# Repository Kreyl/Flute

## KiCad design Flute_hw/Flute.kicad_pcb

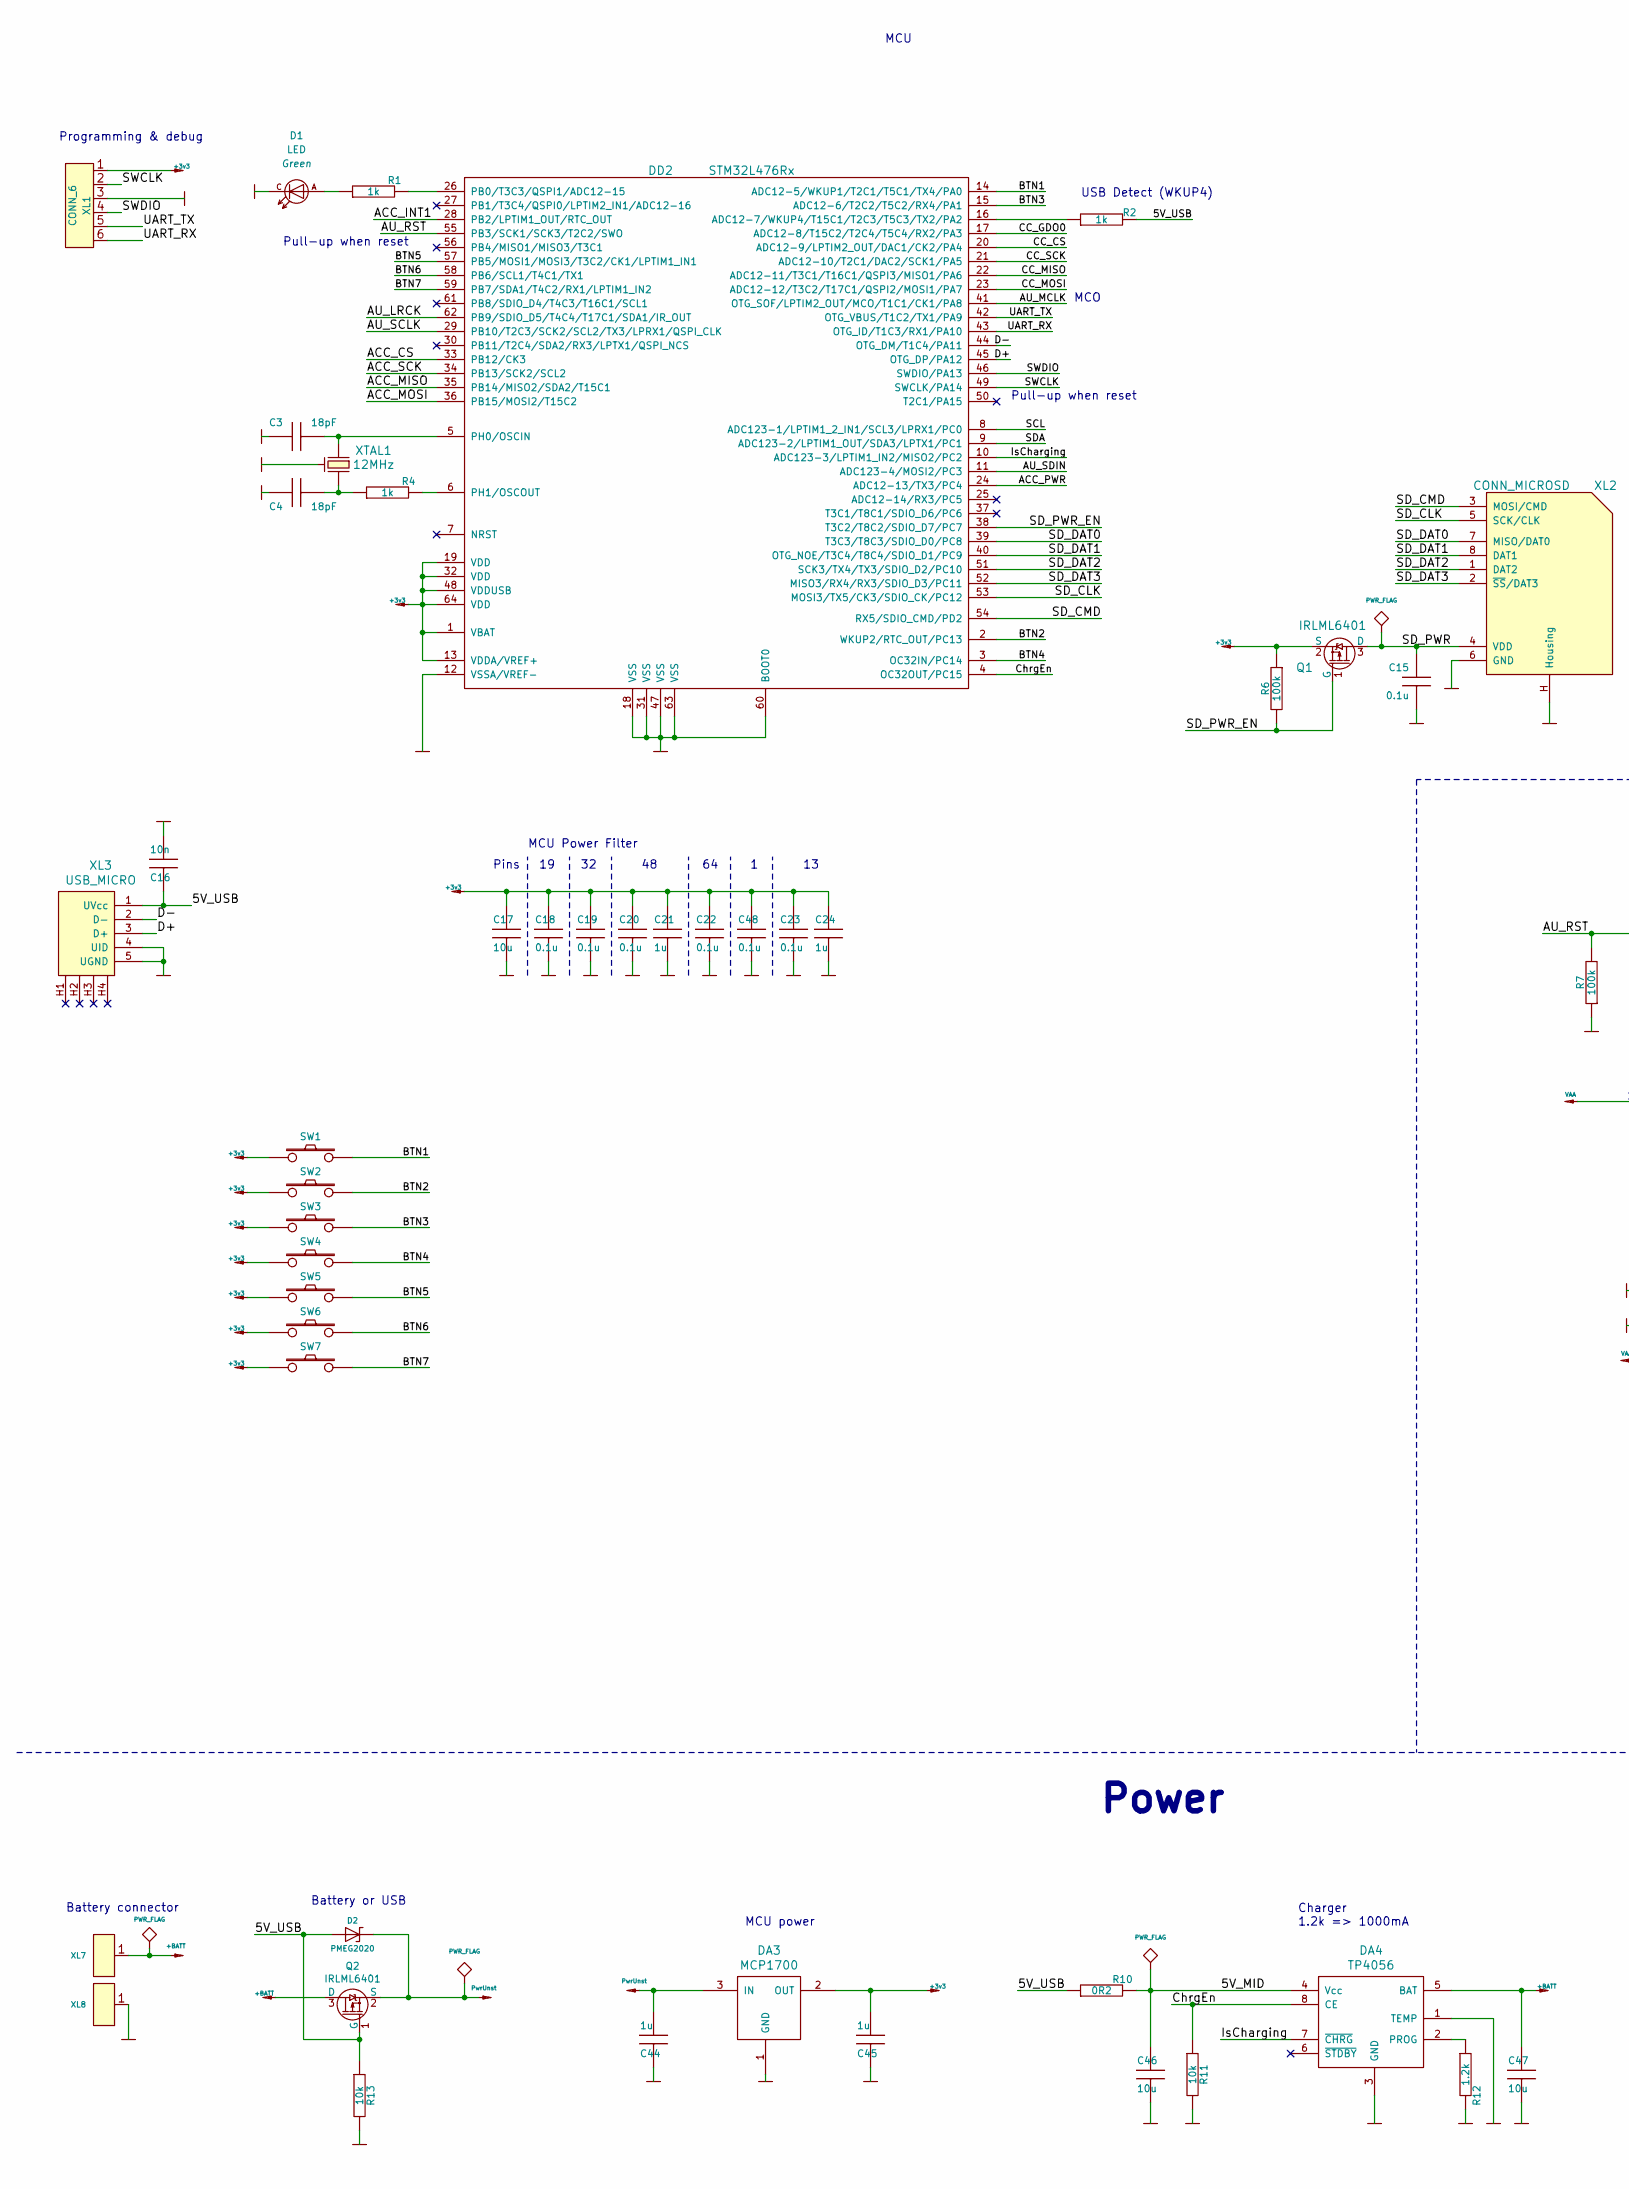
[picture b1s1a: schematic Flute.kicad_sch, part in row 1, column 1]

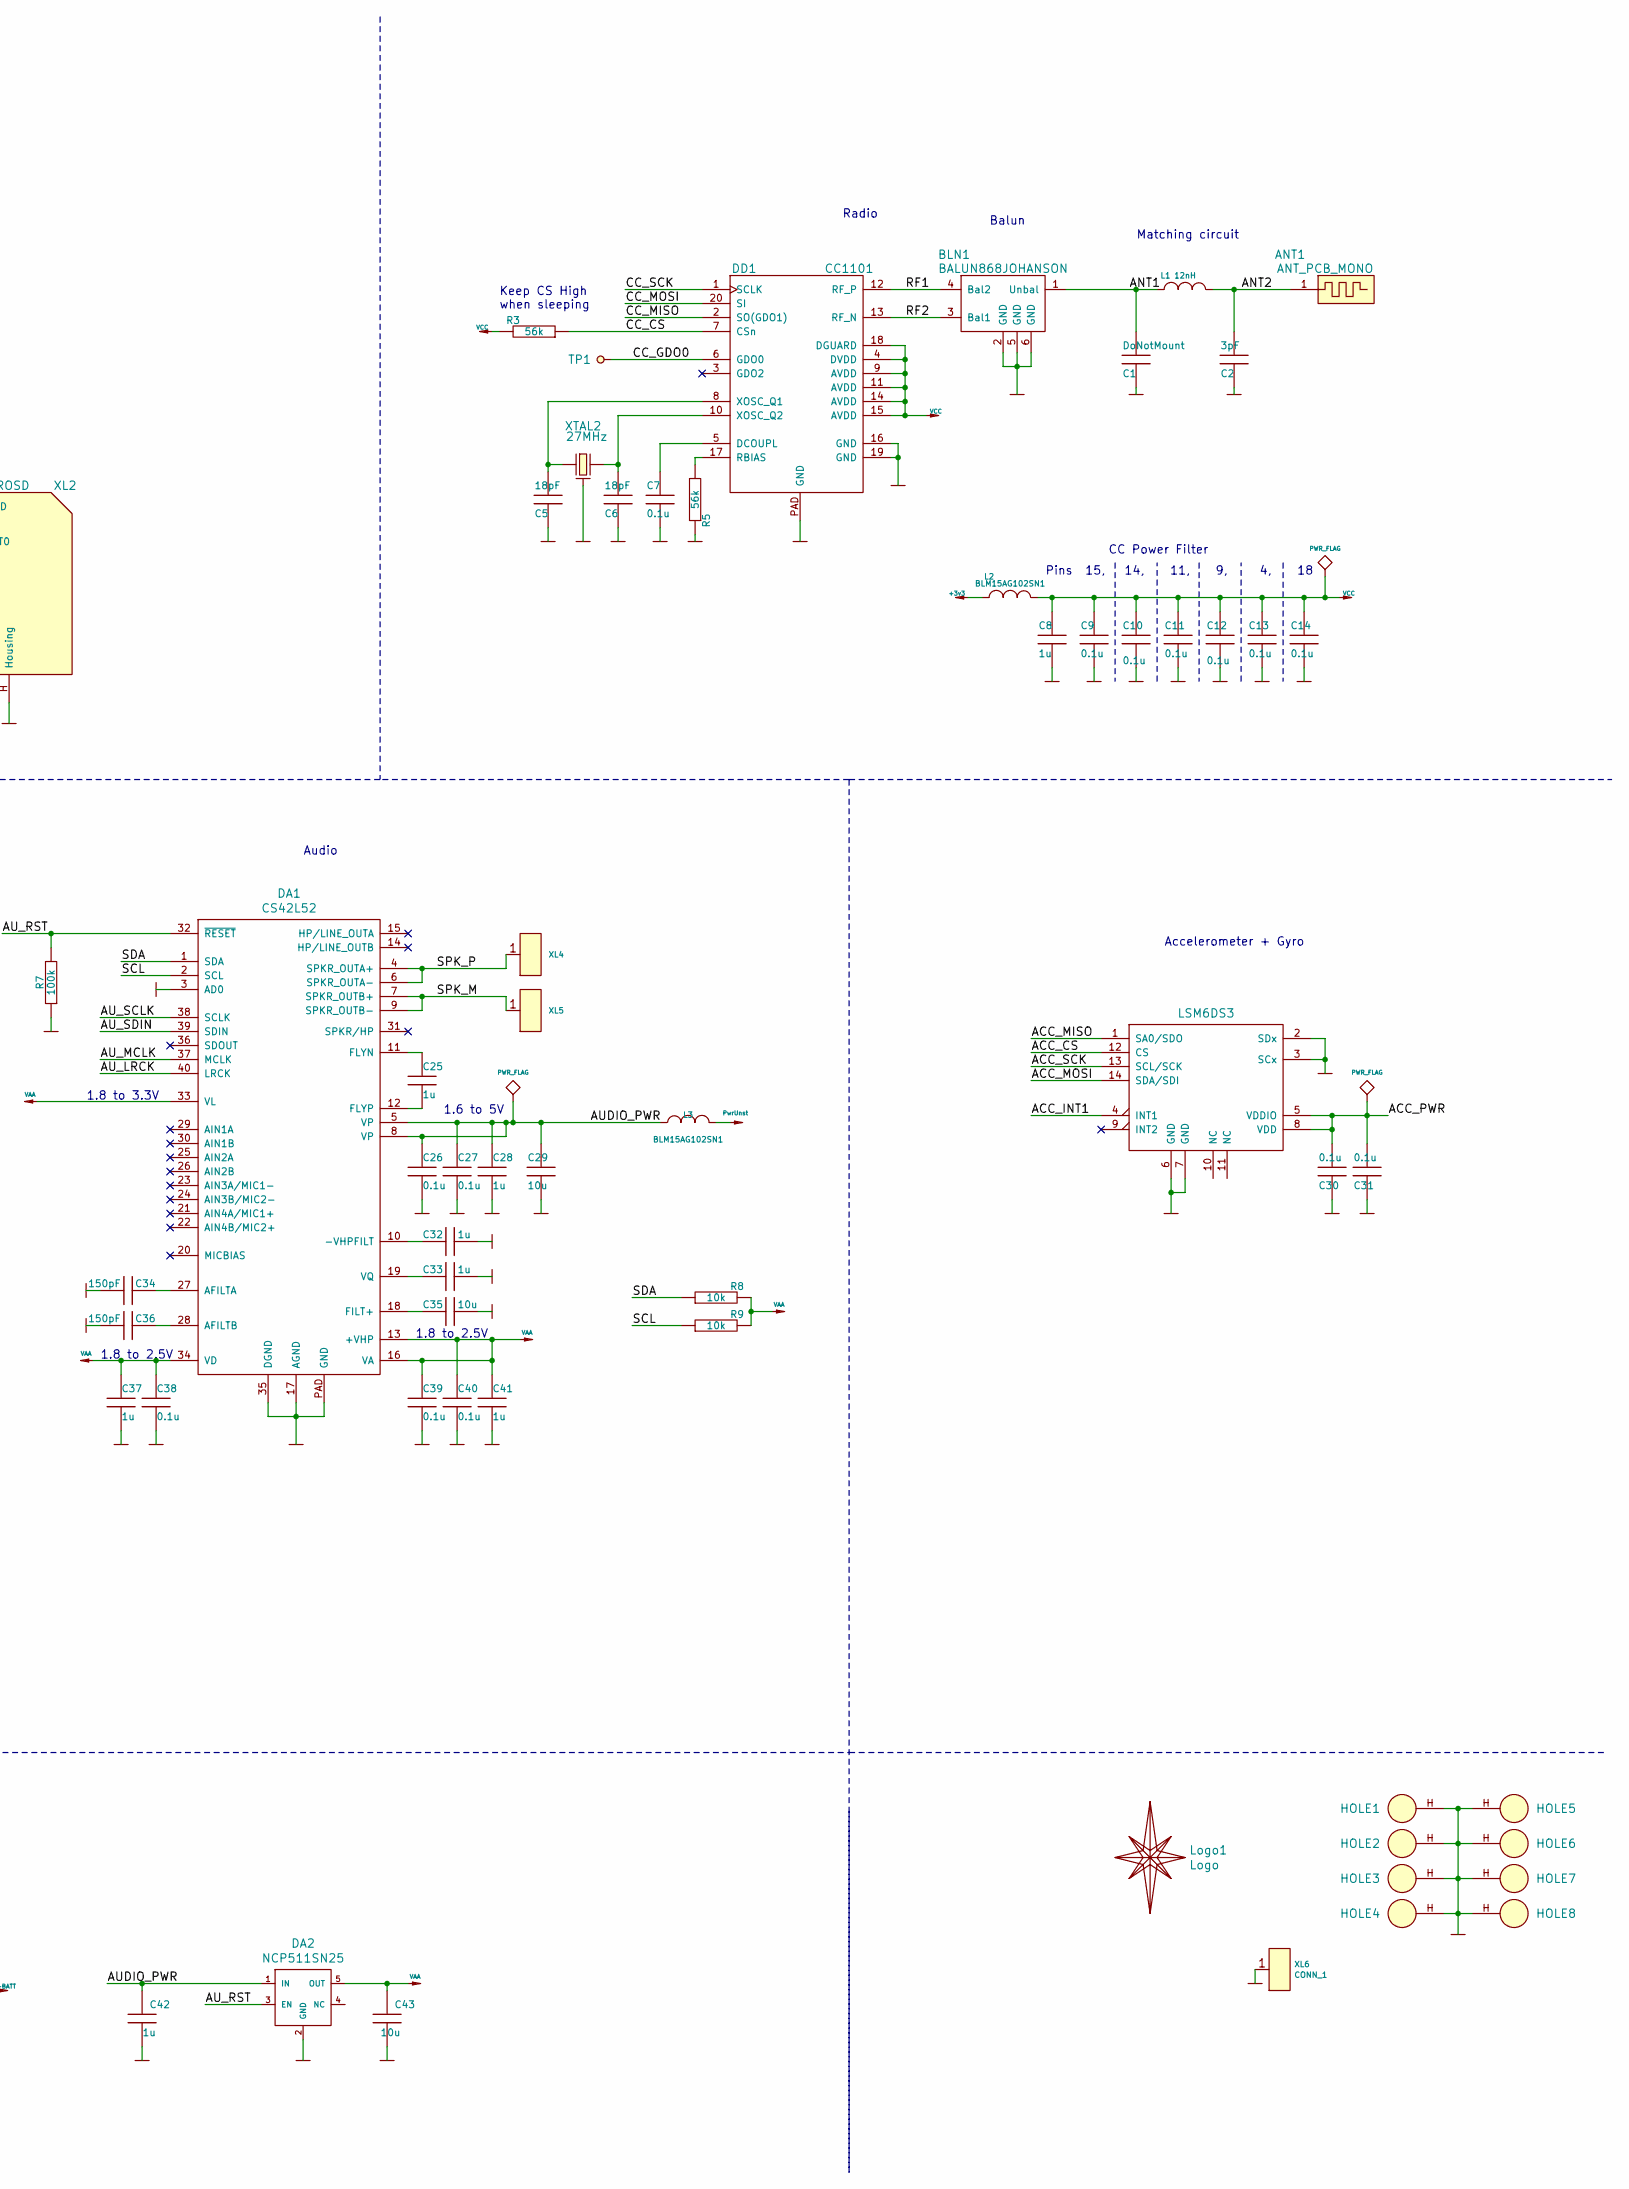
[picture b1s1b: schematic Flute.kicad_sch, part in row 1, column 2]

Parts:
ANT1: ANT_PCB_MONO; Flute_868_inverted
BLN1: BALUN868JOHANSON; BALUN_JOHANSON868
C1: DoNotMount; CAP_0402
C2: 3pF; CAP_0402
C3, C4, C5, C6: 18pF; CAP_0603_Silks
C7, C9, C10, C11, C12, C13, C14, C15, C18, C19, C20, C22, C23, C26, C27, C30, C31, C38, C39, C40, C48: 0.1u; CAP_0603_Silks
C8, C21, C24, C25, C28, C32, C33, C37, C41, C42, C44, C45: 1u; CAP_0603_Silks
C16: 10n; CAP_0603_Silks
C17, C29, C35, C43, C46, C47: 10u; CAP_0603_Silks
C34, C36: 150pF; CAP_0603_Silks
D1: LED; LED_0603
D2: PMEG2020; SOD323
DA1: CS42L52; QFN40
DA2: NCP511SN25; SOT23-5
DA3: MCP1700; SOT23-3A
DA4: TP4056; SO8_150MIL
DD1: CC1101; QFN20
DD2: STM32L476Rx; LQFP64
DD3: LSM6DS3; 14_3x2d5_p0d5
HOLE1, HOLE2, HOLE3, HOLE4, HOLE5, HOLE6, HOLE7, HOLE8: HOLE_METALLED; Hole2d2_out3d5mm
L1: 12nH; IND_0402
L2, L3: BLM15AG102SN1; IND_0402
Logo1: Logo; Ostranna_12d7_10d1
Q1, Q2: IRLML6401; SOT23-3
R1, R2, R4: 1k; RES_0603
R3, R5: 56k; RES_0603
R6, R7: 100k; RES_0603
R8, R9, R11, R13: 10k; RES_0603
R10: 0R2; RES_1206
R12: 1.2k; RES_0603
SW1, SW2, SW3, SW4, SW5, SW6, SW7: BUTTON; BTN_4x4_SMD
TP1: TESTPOINT; TESTPOINT_1MM
XL1: CONN_6; PLS-6_LOCK
XL2: CONN_MICROSD; MICROSD_CAP_FIX05A
XL3: USB_MICRO; USBmicro_MOLEX_1050170001
XL4, XL5: CONN_1; Oval3x1.5
XL6: CONN_1; PLS-1Rnd
XL7, XL8: CONN_1; Square_1MM5
XTAL1: 12MHz; 03225C4
XTAL2: 27MHz; 03225C4

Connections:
+3v3: C17.2, C18.2, C19.2, C20.2, C21.2, C22.2, C23.2, C24.2, C45.1, C48.2, DA3.2 (OUT), DD2.1 (VBAT), DD2.13 (VDDA/VREF+), DD2.19 (VDD), DD2.32 (VDD), DD2.48 (VDDUSB), DD2.64 (VDD), L2.2, Q1.2 (S), R6.1, SW1.1, SW2.1, SW3.1, SW4.1, SW5.1, SW6.1, SW7.1, XL1.1
+BATT: C47.2, DA4.5 (BAT), Q2.3 (D), XL7.1
/5V_MID: C46.2, DA4.4 (Vcc), R10.2
/5V_USB: C16.2, D2.A, Q2.1 (G), R2.2, R10.1, R13.1, XL3.1 (UVcc)
/ACC_CS: DD2.33 (PB12/CK3), DD3.12 (CS)
/ACC_INT1: DD2.28 (PB2/LPTIM1_OUT/RTC_OUT), DD3.4 (INT1)
/ACC_MISO: DD2.35 (PB14/MISO2/SDA2/T15C1), DD3.1 (SA0/SDO)
/ACC_MOSI: DD2.36 (PB15/MOSI2/T15C2), DD3.14 (SDA/SDI)
/ACC_PWR: C30.1, C31.1, DD2.24 (ADC12-13/TX3/PC4), DD3.5 (VDDIO), DD3.8 (VDD)
/ACC_SCK: DD2.34 (PB13/SCK2/SCL2), DD3.13 (SCL/SCK)
/ANT1: BLN1.1 (Unbal), C1.1, L1.2
/ANT2: ANT1.1, C2.1, L1.1
/AUDIO_PWR: C26.1, C27.1, C28.1, C29.2, C42.1, DA1.5 (VP), DA1.8 (VP), DA2.1 (IN), L3.1
/AU_LRCK: DA1.40 (LRCK), DD2.62 (PB9/SDIO_D5/T4C4/T17C1/SDA1/IR_OUT)
/AU_MCLK: DA1.37 (MCLK), DD2.41 (OTG_SOF/LPTIM2_OUT/MCO/T1C1/CK1/PA8)
/AU_RST: DA1.32 (~RESET), DA2.3 (EN), DD2.55 (PB3/SCK1/SCK3/T2C2/SWO), R7.2
/AU_SCLK: DA1.38 (SCLK), DD2.29 (PB10/T2C3/SCK2/SCL2/TX3/LPRX1/QSPI_CLK)
/AU_SDIN: DA1.39 (SDIN), DD2.11 (ADC123-4/MOSI2/PC3)
/BTN1: DD2.14 (ADC12-5/WKUP1/T2C1/T5C1/TX4/PA0), SW1.2
/BTN2: DD2.2 (WKUP2/RTC_OUT/PC13), SW2.2
/BTN3: DD2.15 (ADC12-6/T2C2/T5C2/RX4/PA1), SW3.2
/BTN4: DD2.3 (OC32IN/PC14), SW4.2
/BTN5: DD2.57 (PB5/MOSI1/MOSI3/T3C2/CK1/LPTIM1_IN1), SW5.2
/BTN6: DD2.58 (PB6/SCL1/T4C1/TX1), SW6.2
/BTN7: DD2.59 (PB7/SDA1/T4C2/RX1/LPTIM1_IN2), SW7.2
/CC_CS: DD1.7 (CSn), DD2.20 (ADC12-9/LPTIM2_OUT/DAC1/CK2/PA4), R3.1
/CC_GDO0: DD1.6 (GDO0), DD2.17 (ADC12-8/T15C2/T2C4/T5C4/RX2/PA3), TP1.1
/CC_MISO: DD1.2 (SO(GDO1)), DD2.22 (ADC12-11/T3C1/T16C1/QSPI3/MISO1/PA6)
/CC_MOSI: DD1.20 (SI), DD2.23 (ADC12-12/T3C2/T17C1/QSPI2/MOSI1/PA7)
/CC_SCK: DD1.1 (SCLK), DD2.21 (ADC12-10/T2C1/DAC2/SCK1/PA5)
/ChrgEn: DA4.8 (CE), DD2.4 (OC32OUT/PC15), R11.1
/D+: DD2.45 (OTG_DP/PA12), XL3.3 (D+)
/D-: DD2.44 (OTG_DM/T1C4/PA11), XL3.2 (D-)
/IsCharging: DA4.7 (~CHRG), DD2.10 (ADC123-3/LPTIM1_IN2/MISO2/PC2)
/RF1: BLN1.4 (Bal2), DD1.12 (RF_P)
/RF2: BLN1.3 (Bal1), DD1.13 (RF_N)
/SCL: DA1.2 (SCL), DD2.8 (ADC123-1/LPTIM1_2_IN1/SCL3/LPRX1/PC0), R9.1
/SDA: DA1.1 (SDA), DD2.9 (ADC123-2/LPTIM1_OUT/SDA3/LPTX1/PC1), R8.1
/SD_CLK: DD2.53 (MOSI3/TX5/CK3/SDIO_CK/PC12), XL2.5 (SCK/CLK)
/SD_CMD: DD2.54 (RX5/SDIO_CMD/PD2), XL2.3 (MOSI/CMD)
/SD_DAT0: DD2.39 (T3C3/T8C3/SDIO_D0/PC8), XL2.7 (MISO/DAT0)
/SD_DAT1: DD2.40 (OTG_NOE/T3C4/T8C4/SDIO_D1/PC9), XL2.8 (DAT1)
/SD_DAT2: DD2.51 (SCK3/TX4/TX3/SDIO_D2/PC10), XL2.1 (DAT2)
/SD_DAT3: DD2.52 (MISO3/RX4/RX3/SDIO_D3/PC11), XL2.2 (~SS~/DAT3)
/SD_PWR: C15.1, Q1.3 (D), XL2.4 (VDD)
/SD_PWR_EN: DD2.38 (T3C2/T8C2/SDIO_D7/PC7), Q1.1 (G), R6.2
/SPK_M: DA1.7 (SPKR_OUTB+), DA1.9 (SPKR_OUTB-), XL5.1
/SPK_P: DA1.4 (SPKR_OUTA+), DA1.6 (SPKR_OUTA-), XL4.1
/SWCLK: DD2.49 (SWCLK/PA14), XL1.2
/SWDIO: DD2.46 (SWDIO/PA13), XL1.4
/UART_RX: DD2.43 (OTG_ID/T1C3/RX1/PA10), XL1.6
/UART_TX: DD2.42 (OTG_VBUS/T1C2/TX1/PA9), XL1.5
GND: BLN1.2 (GND), BLN1.5 (GND), BLN1.6 (GND), C1.2, C2.2, C3.2, C4.2, C5.2, C6.2, C7.1, C8.2, C9.2, C10.2, C11.2, C12.2, C13.2, C14.2, C15.2, C16.1, C17.1, C18.1, C19.1, C20.1, C21.1, C22.1, C23.1, C24.1, C26.2, C27.2, C28.2, C29.1, C30.2, C31.2, C32.1, C33.1, C34.1, C35.1, C36.1, C37.2, C38.2, C39.2, C40.2, C41.2, C42.2, C43.2, C44.2, C45.2, C46.1, C47.1, C48.1, D1.C, DA1.3 (AD0), DA1.17 (AGND), DA1.35 (DGND), DA1.PAD (GND), DA2.2 (GND), DA3.1 (GND), DA4.1 (TEMP), DA4.3 (GND), DD1.16 (GND), DD1.19 (GND), DD1.PAD (GND), DD2.12 (VSSA/VREF-), DD2.18 (VSS), DD2.31 (VSS), DD2.47 (VSS), DD2.60 (BOOT0), DD2.63 (VSS), DD3.2 (SDx), DD3.3 (SCx), DD3.6 (GND), DD3.7 (GND), HOLE1.H, HOLE2.H, HOLE3.H, HOLE4.H, HOLE5.H, HOLE6.H, HOLE7.H, HOLE8.H, R5.2, R7.1, R11.2, R12.2, R13.2, XL1.3, XL2.6 (GND), XL2.H (Housing), XL3.4 (UID), XL3.5 (UGND), XL6.1, XL8.1, XTAL1.H, XTAL2.H
unnamed: C3.1, DD2.5 (PH0/OSCIN), XTAL1.1
unnamed: C4.1, R4.1, XTAL1.2
unnamed: C5.1, DD1.8 (XOSC_Q1), XTAL2.1
unnamed: C6.1, DD1.10 (XOSC_Q2), XTAL2.2
unnamed: C7.2, DD1.5 (DCOUPL)
unnamed: C25.1, DA1.11 (FLYN)
unnamed: C25.2, DA1.12 (FLYP)
unnamed: C32.2, DA1.10 (-VHPFILT)
unnamed: C33.2, DA1.19 (VQ)
unnamed: C34.2, DA1.27 (AFILTA)
unnamed: C35.2, DA1.18 (FILT+)
unnamed: C36.2, DA1.28 (AFILTB)
unnamed: D1.A, R1.1
unnamed: DA4.2 (PROG), R12.1
unnamed: DD1.17 (RBIAS), R5.1
unnamed: DD2.6 (PH1/OSCOUT), R4.2
unnamed: DD2.16 (ADC12-7/WKUP4/T15C1/T2C3/T5C3/TX2/PA2), R2.1
unnamed: DD2.26 (PB0/T3C3/QSPI1/ADC12-15), R1.2
PwrUnst: C44.1, D2.C, DA3.3 (IN), L3.2, Q2.2 (S)
VAA: C37.1, C38.1, C39.1, C40.1, C41.1, C43.1, DA1.13 (+VHP), DA1.16 (VA), DA1.33 (VL), DA1.34 (VD), DA2.5 (OUT), R8.2, R9.2
VCC: C8.1, C9.1, C10.1, C11.1, C12.1, C13.1, C14.1, DD1.4 (DVDD), DD1.9 (AVDD), DD1.11 (AVDD), DD1.14 (AVDD), DD1.15 (AVDD), DD1.18 (DGUARD), L2.1, R3.2
no_connect_99: XL3.H1
no_connect_102: XL3.H4

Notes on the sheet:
Programming & debug
Battery connector
Pull-up when reset
Battery or USB
Pins 19 32 48 64 1 13
MCU Power Filter
MCU power
MCU
MCO
USB Detect (WKUP4)
Power
Charger 1.2k => 1000mA
1.8 to 3.3V
1.8 to 2.5V
Audio
1.6 to 5V
Keep CS High when sleeping
Radio
Balun
Pins 15, 14, 11, 9, 4, 18
CC Power Filter
Matching circuit
Accelerometer + Gyro

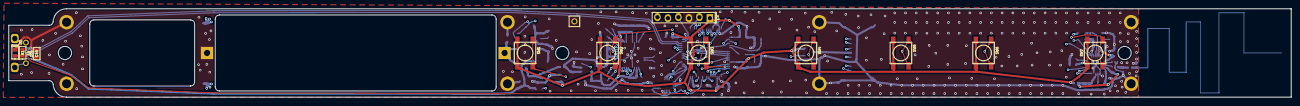
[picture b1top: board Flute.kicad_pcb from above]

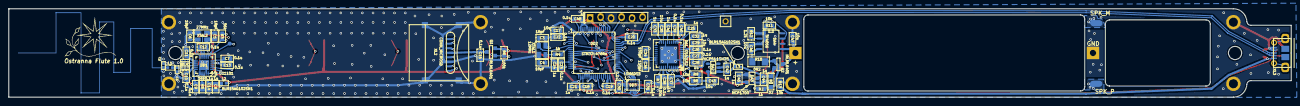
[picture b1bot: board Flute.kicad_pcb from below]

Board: 4 copper layers, 310.5 x 21.4 mm, 104 parts (84 on the bottom side), 74 nets.

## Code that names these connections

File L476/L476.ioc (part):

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Mcu.Name=STM32L476R(C-E-G)Tx
Mcu.Package=LQFP64
Mcu.UserName=STM32L476RCTx
PA0.Mode=SYS_WakeUp0
PA0.Signal=SYS_WKUP1
PA1.Signal=GPIO_Input
PA10.Mode=Asynchronous
PA10.Signal=USART1_RX
PA11.Mode=Device_Only
PA11.Signal=USB_OTG_FS_DM
PA12.Mode=Device_Only
PA12.Signal=USB_OTG_FS_DP
PA13\ (JTMS-SWDIO).Mode=Serial_Wire
PA13\ (JTMS-SWDIO).Signal=SYS_JTMS-SWDIO
PA14\ (JTCK-SWCLK).Mode=Serial_Wire
PA14\ (JTCK-SWCLK).Signal=SYS_JTCK-SWCLK
PA2.Signal=GPIO_Input
PA3.Signal=GPIO_Input
PA4.Signal=GPIO_Output
PA5.Mode=Full_Duplex_Master
PA5.Signal=SPI1_SCK
PA6.Mode=Full_Duplex_Master
PA6.Signal=SPI1_MISO
PA7.Mode=Full_Duplex_Master
PA7.Signal=SPI1_MOSI
PA8.Mode=Clock-out
PA8.Signal=RCC_MCO
PA9.Mode=Asynchronous
PA9.Signal=USART1_TX
PB0.Signal=GPIO_Output
PB10.Mode=SAI_A_AsyncSlave
PB10.Signal=SAI1_SCK_A
PB12.Signal=GPIO_Output
PB13.Mode=Full_Duplex_Master
PB13.Signal=SPI2_SCK
PB14.Mode=Full_Duplex_Master
PB14.Signal=SPI2_MISO
PB15.Mode=Full_Duplex_Master
PB15.Signal=SPI2_MOSI
PB2.Signal=GPIO_Input
PB3\ (JTDO-TRACESWO).Signal=GPIO_Output
PB9.Mode=SAI_A_AsyncSlave
PB9.Signal=SAI1_FS_A
PC0.Mode=I2C
PC0.Signal=I2C3_SCL
PC1.Mode=I2C
PC1.Signal=I2C3_SDA
PC10.Mode=SD_4_bits_Wide_bus
PC10.Signal=SDMMC1_D2
PC11.Mode=SD_4_bits_Wide_bus
PC11.Signal=SDMMC1_D3
PC12.Mode=SD_4_bits_Wide_bus
PC12.Signal=SDMMC1_CK
PC13.Mode=SYS_WakeUp1
PC13.Signal=SYS_WKUP2
PC14-OSC32_IN\ (PC14).Signal=GPIO_Input
PC15-OSC32_OUT\ (PC15).Signal=GPIO_Input
PC2.Signal=GPIO_Input
PC3.Mode=SAI_A_AsyncSlave
PC3.Signal=SAI1_SD_A
PC4.Signal=GPIO_Output
PC7.Signal=GPIO_Output
PC8.Mode=SD_4_bits_Wide_bus
PC8.Signal=SDMMC1_D0
PC9.Mode=SD_4_bits_Wide_bus
PC9.Signal=SDMMC1_D1
PD2.Mode=SD_4_bits_Wide_bus
PD2.Signal=SDMMC1_CMD
PH0-OSC_IN\ (PH0).Mode=HSE-External-Oscillator
PH0-OSC_IN\ (PH0).Signal=RCC_OSC_IN
PH1-OSC_OUT\ (PH1).Mode=HSE-External-Oscillator
PH1-OSC_OUT\ (PH1).Signal=RCC_OSC_OUT
RCC.HSE_VALUE=8000000
board=custom

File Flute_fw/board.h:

/*
 * board.h
 *
 *  Created on: 05 08 2018
 *      Author: Kreyl
 */

#ifndef BOARD_H__
#define BOARD_H__

// ==== General ====
#define APP_NAME            "Flute"

// Version of PCB
#define PCB_VER                 1

// MCU type as defined in the ST header.
#define STM32L476xx

// Freq of external crystal if any. Leave it here even if not used.
#define CRYSTAL_FREQ_HZ         12000000

// OS timer settings
#define STM32_ST_IRQ_PRIORITY   2
#define STM32_ST_USE_TIMER      5
#define SYS_TIM_CLK             (Clk.APB1FreqHz)    // Timer 5 is clocked by APB1

//  Periphery
#define I2C1_ENABLED            FALSE
#define I2C2_ENABLED            FALSE
#define I2C3_ENABLED            TRUE

#define ADC_REQUIRED            FALSE
#define STM32_DMA_REQUIRED      TRUE    // Leave this macro name for OS

#if 1 // ========================== GPIO =======================================
// EXTI
#define INDIVIDUAL_EXTI_IRQ_REQUIRED    FALSE

// Buttons
#define BTN1_PIN        GPIOA, 0, pudPullDown
#define BTN2_PIN        GPIOC, 13, pudPullDown
#define BTN3_PIN        GPIOA, 1, pudPullDown
#define BTN4_PIN        GPIOC, 14, pudPullDown
#define BTN5_PIN        GPIOB, 5, pudPullDown
#define BTN6_PIN        GPIOB, 6, pudPullDown
#define BTN7_PIN        GPIOB, 7, pudPullDown

// Charging
#define CHRG_EN_PIN     GPIOC, 15
#define IS_CHARGING_PIN GPIOC, 2

// UART
#define UART_GPIO       GPIOA
#define UART_TX_PIN     9
#define UART_RX_PIN     10

// LED
#define LED_BTN         { GPIOB, 0, TIM3, 3, invNotInverted, omPushPull, 255 }

// CS42L52
#define AU_RESET        GPIOB, 3, omPushPull
#define AU_MCLK         GPIOA, 8, omPushPull, pudNone, AF0  // MCO
#define AU_SDIN         GPIOC, 3, omPushPull, pudNone, AF13 // MOSI; SAI1_A
#define AU_LRCK         GPIOB, 9, omPushPull, pudNone, AF13
#define AU_SCLK         GPIOB, 10, omPushPull, pudNone, AF13
#define AU_i2c          i2c3
#define AU_SAI          SAI1
#define AU_SAI_A        SAI1_Block_A
#define AU_SAI_B        SAI1_Block_B
#define AU_SAI_RccEn()  RCC->APB2ENR |= RCC_APB2ENR_SAI1EN
#define AU_SAI_RccDis() RCC->APB2ENR &= ~RCC_APB2ENR_SAI1EN

// Acc
#define ACG_IRQ_PIN     GPIOB, 2
#define ACG_CS_PIN      GPIOB, 12
#define ACG_SCK_PIN     GPIOB, 13, omPushPull, pudNone, AF5
#define ACG_MISO_PIN    GPIOB, 14, omPushPull, pudNone, AF5
#define ACG_MOSI_PIN    GPIOB, 15, omPushPull, pudNone, AF5
#define ACG_PWR_PIN     GPIOC, 4
#define ACG_SPI         SPI2

// I2C
#define I2C1_GPIO       GPIOB
#define I2C1_SCL        6
#define I2C1_SDA        7
#define I2C2_GPIO       GPIOB
#define I2C2_SCL        10
#define I2C2_SDA        11
#define I2C3_GPIO       GPIOC
#define I2C3_SCL        0
#define I2C3_SDA        1
// I2C Alternate Function
#define I2C_AF          AF4

// USB
#define USB_DM          GPIOA, 11
#define USB_DP          GPIOA, 12
#define USB_AF          AF10
// USB detect
#define USB_DETECT_PIN  GPIOA, 2

// SD
#define SD_PWR_PIN      GPIOC, 7
#define SD_AF           AF12
#define SD_DAT0         GPIOC,  8, omPushPull, pudPullUp, SD_AF
#define SD_DAT1         GPIOC,  9, omPushPull, pudPullUp, SD_AF
#define SD_DAT2         GPIOC, 10, omPushPull, pudPullUp, SD_AF
#define SD_DAT3         GPIOC, 11, omPushPull, pudPullUp, SD_AF
#define SD_CLK          GPIOC, 12, omPushPull, pudNone,   SD_AF
#define SD_CMD          GPIOD,  2, omPushPull, pudPullUp, SD_AF

// Radio: SPI, PGpio, Sck, Miso, Mosi, Cs, Gdo0
#define CC_Setup0       SPI1, GPIOA, 5,6,7, GPIOA,4, GPIOA,3

#endif // GPIO

#if 1 // =========================== I2C =======================================
// i2cclkPCLK1, i2cclkSYSCLK, i2cclkHSI
#define I2C_CLK_SRC     i2cclkHSI
#define I2C_BAUDRATE_HZ 400000
#endif

#if ADC_REQUIRED // ======================= Inner ADC ==========================
// Clock divider: clock is generated from the APB2
#define ADC_CLK_DIVIDER		adcDiv2

// ADC channels
#define ADC_BATTERY_CHNL 	14
// ADC_VREFINT_CHNL
#define ADC_CHANNELS        { ADC_BATTERY_CHNL, ADC_VREFINT_CHNL }
#define ADC_CHANNEL_CNT     2   // Do not use countof(AdcChannels) as preprocessor does not know what is countof => cannot check
#define ADC_SAMPLE_TIME     ast24d5Cycles
#define ADC_OVERSAMPLING_RATIO  64   // 1 (no oversampling), 2, 4, 8, 16, 32, 64, 128, 256
#endif

#if 1 // =========================== DMA =======================================
// ==== Uart ====
// Remap is made automatically if required
#define UART_DMA_TX     STM32_DMA_STREAM_ID(2, 6)
#define UART_DMA_RX     STM32_DMA_STREAM_ID(2, 7)
#define UART_DMA_CHNL   2
#define UART_DMA_TX_MODE(Chnl) (STM32_DMA_CR_CHSEL(Chnl) | DMA_PRIORITY_LOW | STM32_DMA_CR_MSIZE_BYTE | STM32_DMA_CR_PSIZE_BYTE | STM32_DMA_CR_MINC | STM32_DMA_CR_DIR_M2P | STM32_DMA_CR_TCIE)
#define UART_DMA_RX_MODE(Chnl) (STM32_DMA_CR_CHSEL(Chnl) | DMA_PRIORITY_MEDIUM | STM32_DMA_CR_MSIZE_BYTE | STM32_DMA_CR_PSIZE_BYTE | STM32_DMA_CR_MINC | STM32_DMA_CR_DIR_P2M | STM32_DMA_CR_CIRC)

// ==== ACG ====
#define ACG_DMA_TX      STM32_DMA_STREAM_ID(1, 5)
#define ACG_DMA_RX      STM32_DMA_STREAM_ID(1, 4)
#define ACG_DMA_CHNL    1

// ==== I2C ====
#define I2C1_DMA_TX     STM32_DMA_STREAM_ID(1, 6)
#define I2C1_DMA_RX     STM32_DMA_STREAM_ID(1, 7)
#define I2C1_DMA_CHNL   3
#define I2C2_DMA_TX     STM32_DMA_STREAM_ID(1, 4)
#define I2C2_DMA_RX     STM32_DMA_STREAM_ID(1, 5)
#define I2C2_DMA_CHNL   3
#define I2C3_DMA_TX     STM32_DMA_STREAM_ID(1, 2)
#define I2C3_DMA_RX     STM32_DMA_STREAM_ID(1, 3)
#define I2C3_DMA_CHNL   3

// ==== SAI ====
#define SAI_DMA_A       STM32_DMA_STREAM_ID(2, 1)
#define SAI_DMA_CHNL    1

// ==== SDMMC ====
#define STM32_SDC_SDMMC1_DMA_STREAM   STM32_DMA_STREAM_ID(2, 5)

#if ADC_REQUIRED
#define ADC_DMA         STM32_DMA1_STREAM1
#define ADC_DMA_MODE    STM32_DMA_CR_CHSEL(0) |   /* DMA1 Stream1 Channel0 */ \
                        DMA_PRIORITY_LOW | \
                        STM32_DMA_CR_MSIZE_HWORD | \
                        STM32_DMA_CR_PSIZE_HWORD | \
                        STM32_DMA_CR_MINC |       /* Memory pointer increase */ \
                        STM32_DMA_CR_DIR_P2M |    /* Direction is peripheral to memory */ \
                        STM32_DMA_CR_TCIE         /* Enable Transmission Complete IRQ */
#endif // ADC

#endif // DMA

#if 1 // ========================== USART ======================================
#define PRINTF_FLOAT_EN TRUE
#define UART_TXBUF_SZ   4096
#define UART_RXBUF_SZ   99

#define UARTS_CNT       1

#define CMD_UART_PARAMS \
    USART1, UART_GPIO, UART_TX_PIN, UART_GPIO, UART_RX_PIN, \
    UART_DMA_TX, UART_DMA_RX, UART_DMA_TX_MODE(UART_DMA_CHNL), UART_DMA_RX_MODE(UART_DMA_CHNL), \
    uartclkHSI // Use independent clock

#endif

#endif //BOARD_H__

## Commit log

2020-12-30 Sch done
2021-01-04 + Layout done
2021-01-08 PCB sent to production
2021-01-19 + FW plays ALIVE.WAV, but not loud enough
2021-02-06 Plays what needed
2021-02-06 + Play with timeout
2021-02-07 + Low freq mode + Standby RC
2021-11-01 + Long press for wakeup returned - Repeated play timeout removed
2021-12-03 + Radio
2022-05-04 Btn indx sent by radio
2022-05-26 + Radio pwr in settings.ini
2022-07-31 - FluteSnd + Combo 6+smth, 7+smth
2022-08-03 Playing 15 files: 1..5 by btn, 6..10 by Btn + Btn6, 11..15 by Btn + Btn7
2022-08-03 + 1+2 btn = stop
2022-08-07 Volume increased
2024-07-29 Switch to Eclipse. Compiled.
2024-07-29 Replace pragma once
2024-07-30 Many buttons
2024-07-30 Release
